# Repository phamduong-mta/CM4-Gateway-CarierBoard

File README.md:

# CM4 Security Gateway Rev B — GÓI FINAL (giai đoạn 2)

Xuất lúc 2026-11-19 14:27 · commit `5cdd320` (file chưa commit: 29) · KiCad 10.0.6

Bo mạch mang cho Raspberry Pi CM4 (eMMC, không WiFi): 1 WAN + 4 LAN Gigabit, USB-A, USB-C nạp eMMC, console micro-USB,
TPM 2.0, RTC, SRAM giữ khóa bị xóa khi mở vỏ (switch bàn phím cơ). 150 × 105 mm, 6 lớp, ENIG, nguồn 12 V DC.

## Trạng thái

| Hạng mục | Kết quả |
|---|---|
| ERC schematic | **0 lỗi**, 0 cảnh báo |
| DRC PCB (đã đi dây) | **0 lỗi**, 0 cảnh báo |
| Chưa nối | **0** |
| Lệch schematic ↔ PCB | **0** |
| Luật DRC theo Reference | không có |
| Linh kiện | 420 footprint; BOM JLC 397 = CPL 397 → đạt |
| Chân CM4 có nối | 100 / 200 |
| Tiền linh kiện | ≈ 56.7 USD/bo (5 bo, chưa gồm CM4, PCB, công lắp) |

## Đặt mạch: làm theo `06_fabrication/ORDERING.md`

Ba file cần tải lên JLCPCB: `06_fabrication/gerber.zip`, `bom_jlc.csv`, `cpl_jlc.csv`.
Trước khi thanh toán phải xem lại chiều xoay linh kiện ở màn hình xem trước của JLC (mục 4 của ORDERING.md).

## Nên xem

1. `03_images/3d_iso.png`, `3d_top.png`, `3d_bottom.png`, `3d_front.png`, `3d_back.png` — hình dạng bo.
2. `03_images/copper_L1…L6.png` — từng lớp đồng; `02_pcb_drawings/` — PDF từng lớp, bản vẽ lắp ráp, kích thước.
3. `01_schematic/cm4-gateway-schematic.pdf` — nguyên lý.
4. `05_reports/SUMMARY.md`, `routing-report.md` — DRC/ERC, độ dài và độ lệch từng cặp vi sai.
5. `09_docs/BRINGUP.md` — cấp nguồn lần đầu, nạp eMMC, thử từng khối, thử chống mở vỏ.
6. `09_docs/SOFTWARE.md` — `config.txt`, PCIe/NIC, TPM, RTC, SRAM + GPIO tamper.
7. `09_docs/design-doc.md`, `decisions.md` — thiết kế và mọi quyết định (kể cả thay đổi ở giai đoạn 2).

## Thay đổi so với gói giai đoạn 1 đã duyệt

- **Công tắc chống mở vỏ**: theo phản hồi của chủ dự án — Kailh Red (C49234236), model 3D switch bàn phím cơ thật.
  Nhấn (vỏ đậy) = thông mạch; nhả (mở vỏ) = ngắt → SRAM mất cả VCC lẫn VBAT.
- **Đảo cực P/N tại mọi đầu thu PCIe** (chuẩn PCIe cho phép, không cần cấu hình phần mềm) để cặp vi sai không bắt chéo.
- **Đổi gán cổng xuôi của switch** (SW1: cổng 1 → LAN2, cổng 2 → LAN1; SW2: cổng 1 → LAN4, cổng 2 → LAN3).
- **Dời linh kiện bên trong bo**: SW2 sang trái 6.4 mm; tụ AC và điện trở clock xếp thành cặp cạnh chân; khu USB xếp lại.
  Vị trí mọi cổng mặt trước/sau, kích thước bo và lỗ bắt vít **không đổi**.
- Chi tiết và lý do: `09_docs/decisions.md` (các dòng "(GĐ2)").

## Rủi ro còn mở (chi tiết ở design-doc §11)

- **R1** — chưa có bằng chứng công khai PI7C9X2G404SL ghép tầng chạy với CM4 (về nguyên tắc là cầu PCIe chuẩn).
- **R2** — mạch phân cực lại clock PCIe của CM4 chưa đo thực tế (đo ở BRINGUP bước 6).
- **R7** — bề rộng đường theo trở kháng tính bằng công thức gần đúng; cần chọn đúng stackup JLC06161H-3313 khi đặt.
- **Góc xoay CPL** chưa kiểm chứng được ngoại tuyến → xem lại trên trang JLC.
- Bản đi dây do script sinh, đã qua DRC của KiCad và review độc lập bằng máy; **chưa có người rà layout** — nên đặt
  số lượng nhỏ (5 bo) cho lần đầu.

## Cấu trúc gói

```
01_schematic/      PDF toàn bộ sheet + SVG
02_pcb_drawings/   PDF từng lớp đồng, bản vẽ lắp ráp top/bottom, kích thước, floorplan
03_images/         render 3D 5 góc, ảnh từng lớp đồng, sơ đồ khối, cây nguồn
04_3d/             STEP đầy đủ
05_reports/        ERC + DRC (rpt + json), tóm tắt, báo cáo đi dây
06_fabrication/    gerber.zip (+ thư mục gerber, bản đồ khoan), bom_jlc.csv, cpl_jlc.csv, lcsc_map.csv, ORDERING.md
07_bom_netlist/    BOM đầy đủ kèm tồn kho/giá, netlist, toạ độ mọi linh kiện
08_source/         nguồn KiCad + thư viện + model 3D + toàn bộ script sinh thiết kế
09_docs/           design doc, bảng chân CM4, driver-check, BRINGUP.md, SOFTWARE.md, quyết định, review
```

Sinh lại toàn bộ từ nguồn: `python3 scripts/gen/design.py && python3 scripts/gen/board.py &&
git show 5cdd320:hardware/cm4-gateway.kicad_pcb > /tmp/revA.kicad_pcb && .venv/bin/python scripts/gen/reuse_route.py /tmp/revA.kicad_pcb && .venv/bin/python scripts/gen/finish.py 8 && .venv/bin/python scripts/gen/patch_rev_b.py && python3 scripts/gen/polish_rev_b.py hardware/cm4-gateway.kicad_pcb && python3 scripts/export_release.py` (Rev B giữ nguyên dây của Rev A ngoài khu nguồn, chỉ đi lại khu nguồn; Rev A sinh bằng `route.py` + `patch_rev_a.py`).

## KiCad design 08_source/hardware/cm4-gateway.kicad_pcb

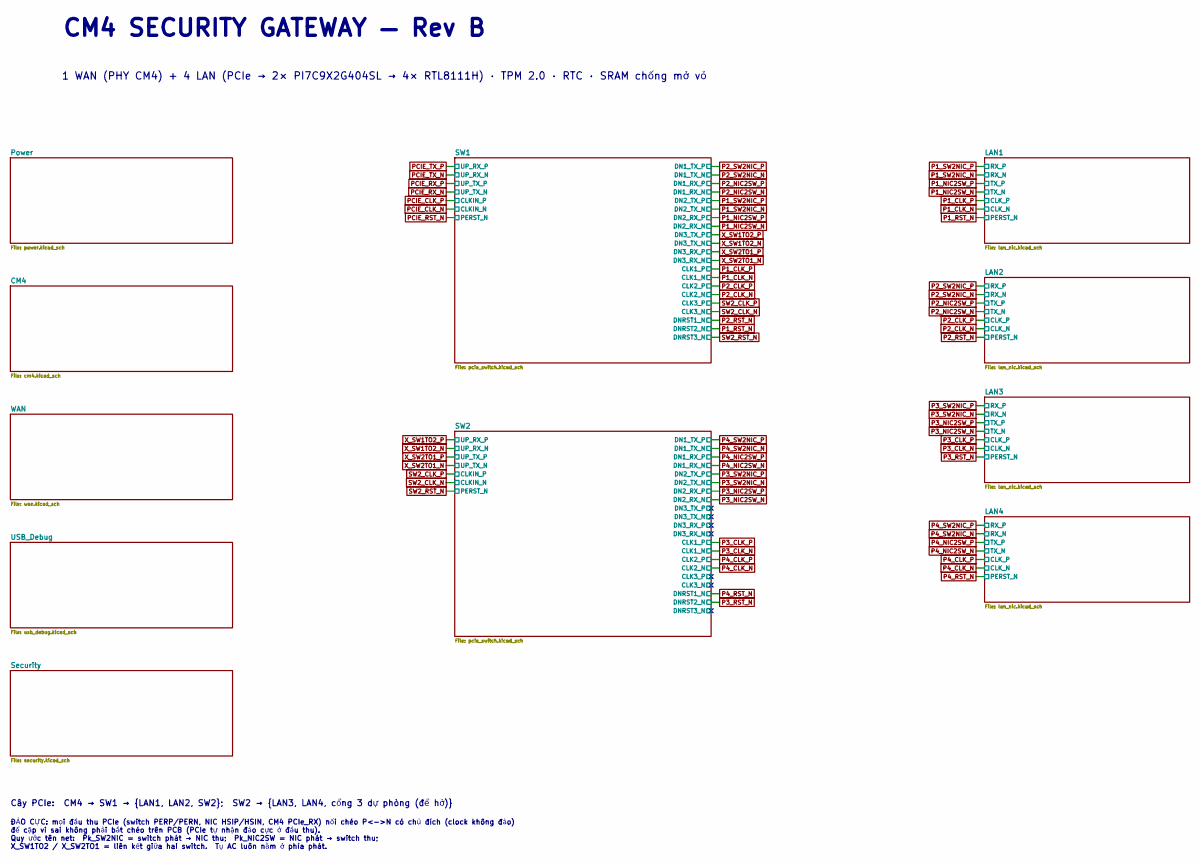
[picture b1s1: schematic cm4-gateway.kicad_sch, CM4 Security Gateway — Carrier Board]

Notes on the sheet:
CM4 SECURITY GATEWAY — Rev B
1 WAN (PHY CM4) + 4 LAN (PCIe → 2× PI7C9X2G404SL → 4× RTL8111H) · TPM 2.0 · RTC · SRAM chống mở vỏ
Cây PCIe: CM4 → SW1 → {LAN1, LAN2, SW2}; SW2 → {LAN3, LAN4, cổng 3 dự phòng (để hở)}
ĐẢO CỰC: mọi đầu thu PCIe (switch PERP/PERN, NIC HSIP/HSIN, CM4 PCIe_RX) nối chéo P<->N có chủ đích (clock không đảo) để cặp vi sai không phải bắt chéo trên PCB (PCIe tự nhận đảo cực ở đầu thu). Quy ước tên net: Pk_SW2NIC = switch phát → NIC thu; Pk_NIC2SW = NIC phát → switch thu; X_SW1TO2 / X_SW2T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

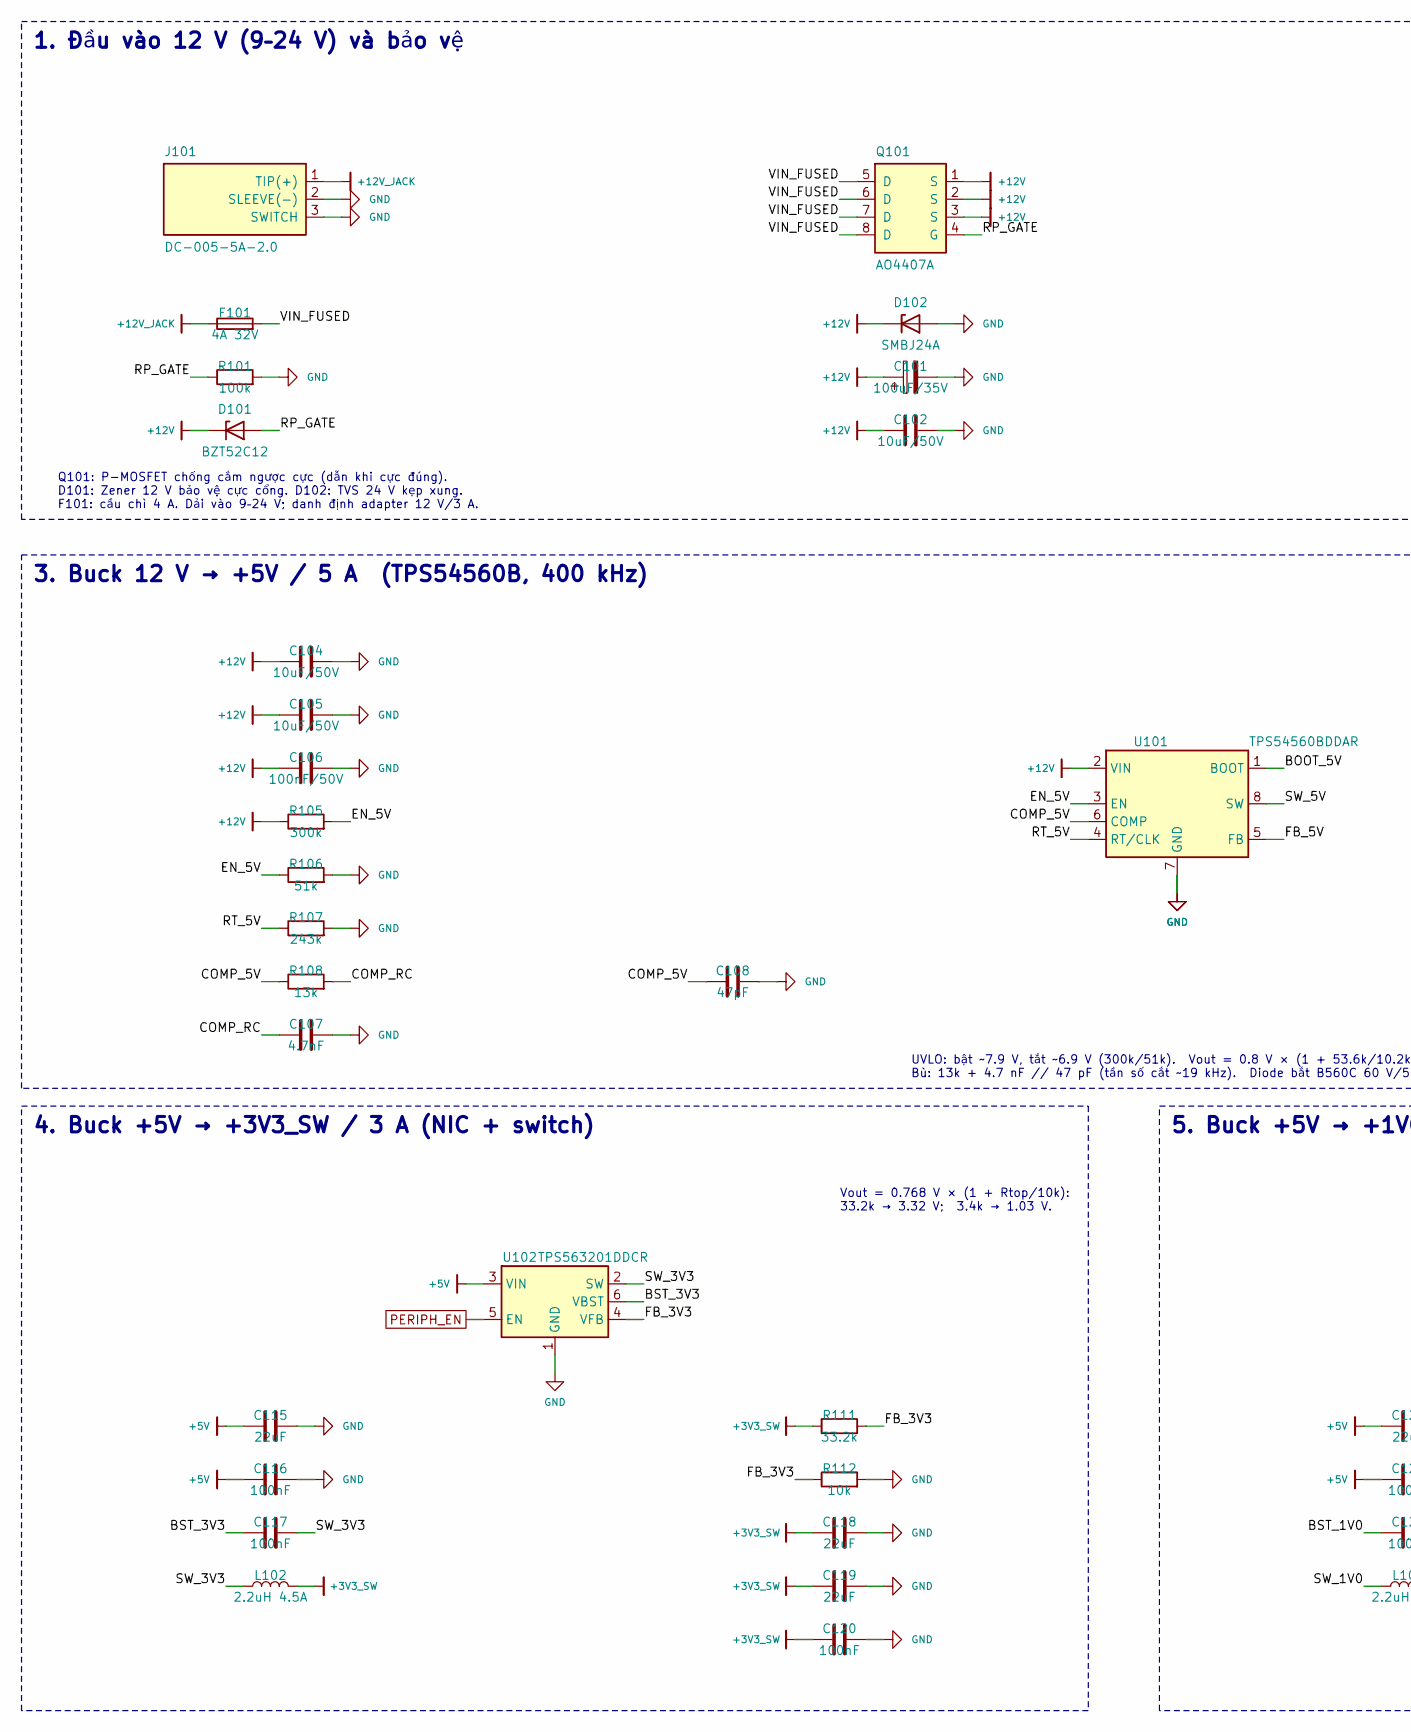
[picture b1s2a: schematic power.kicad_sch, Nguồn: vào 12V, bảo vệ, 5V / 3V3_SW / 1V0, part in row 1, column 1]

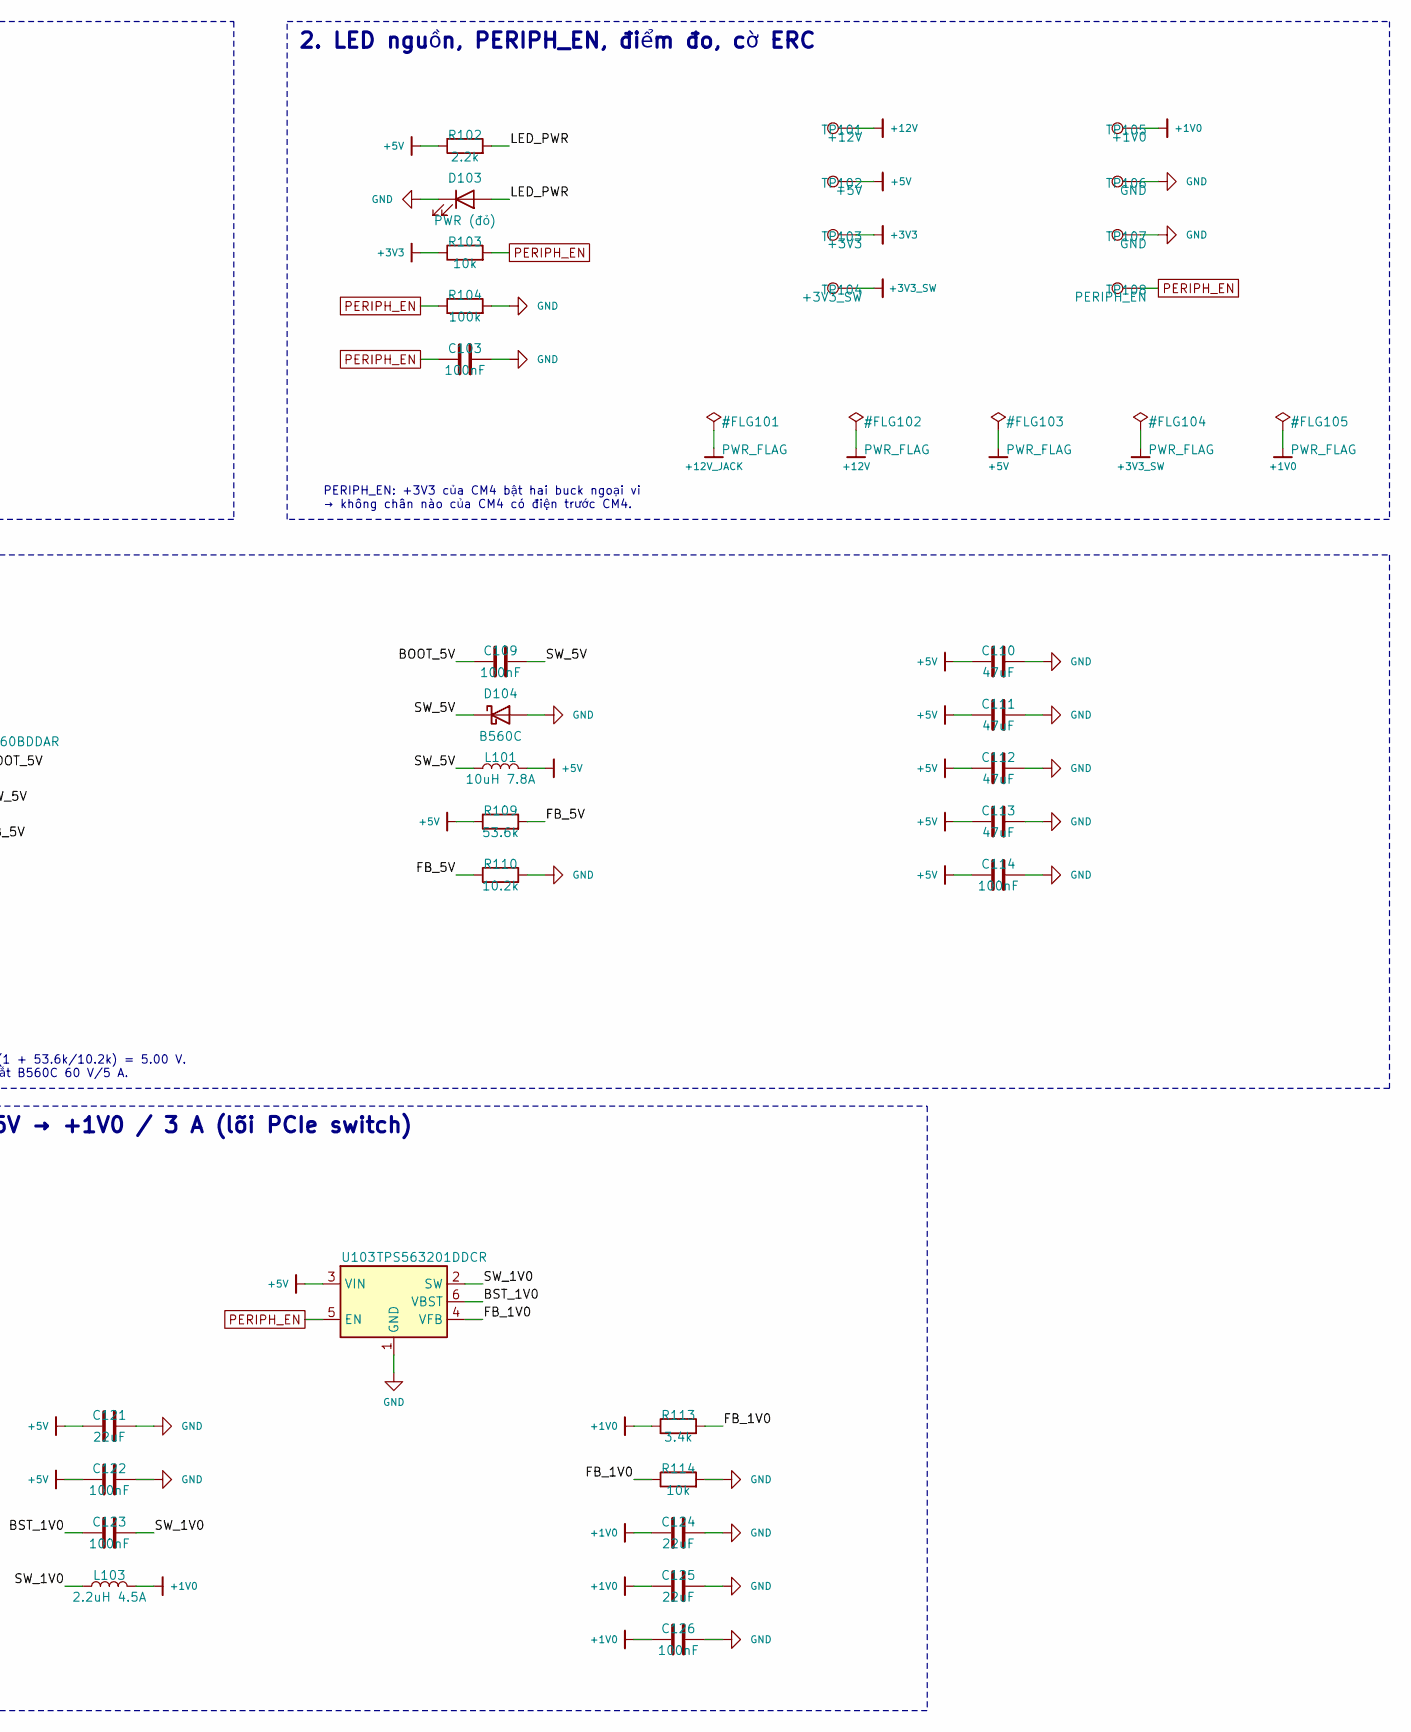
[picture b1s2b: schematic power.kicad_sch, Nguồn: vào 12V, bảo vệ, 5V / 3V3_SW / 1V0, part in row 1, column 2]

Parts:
C101: 100uF/35V; CP_Elec_6.3x7.7; MPN VZH101M1VTR-0607; LCSC C176683
C102, C104, C105: 10uF/50V; C_1206_3216Metric; MPN CL31A106KBHNNNE; LCSC C13585
C103, C109, C114, C116, C117, C120, C122, C123, C126: 100nF; C_0402_1005Metric; MPN CL05B104KO5NNNC; LCSC C1525
C106: 100nF/50V; C_0402_1005Metric; MPN GRM155R71H104KE14D; LCSC C77020
C107: 4.7nF; C_0402_1005Metric; MPN CL05B472KB5NNNC; LCSC C84705
C108: 47pF; C_0402_1005Metric; MPN CL05C470JB5NNNC; LCSC C84706
C110, C111, C112, C113: 47uF; C_1206_3216Metric; MPN CL31A476MPHNNNE; LCSC C96123
C115, C118, C119, C121, C124, C125: 22uF; C_0805_2012Metric; MPN CL21A226MAQNNNE; LCSC C45783
D101: BZT52C12; D_SOD-123; MPN BZT52C12; LCSC C43491
D102: SMBJ24A; D_SMB; MPN SMBJ24A; LCSC C123819
D103: PWR (đỏ); LED_0603_1608Metric; MPN KT-0603R; LCSC C2286
D104: B560C; D_SMC; MPN B560C-13-F; LCSC C85100
F101: 4A 32V; Fuse_1206_3216Metric; MPN 0466004.NRHF; LCSC C187596
J101: DC-005-5A-2.0; BarrelJack_XKB_DC-005-5A; MPN DC-005-5A-2.0; LCSC C381116
L101: 10uH 7.8A; L_Changjiang_FXL1040; MPN FXL1040-100-M; LCSC C475915
L102, L103: 2.2uH 4.5A; L_Changjiang_FXL0420; MPN FXL0420-2R2-M; LCSC C167206
Q101: AO4407A; SOIC-8_3.9x4.9mm_P1.27mm; MPN AO4407A; LCSC C16072
R101, R104: 100k; R_0402_1005Metric; MPN 0402WGF1003TCE; LCSC C25741
R102: 2.2k; R_0402_1005Metric; MPN 0402WGF2201TCE; LCSC C25879
R103, R112, R114: 10k; R_0402_1005Metric; MPN 0402WGF1002TCE; LCSC C25744
R105: 300k; R_0402_1005Metric; MPN 0402WGF3003TCE; LCSC C25774
R106: 51k; R_0402_1005Metric; MPN 0402WGF5102TCE; LCSC C25794
R107: 243k; R_0402_1005Metric; MPN 0402WGF2433TCE; LCSC C43249
R108: 13k; R_0402_1005Metric; MPN 0402WGF1302TCE; LCSC C25754
R109: 53.6k; R_0402_1005Metric; MPN 0402WGF5362TCE; LCSC C53398
R110: 10.2k; R_0402_1005Metric; MPN 0402WGF1022TCE; LCSC C11660
R111: 33.2k; R_0402_1005Metric; MPN 0402WGF3322TCE; LCSC C122548
R113: 3.4k; R_0402_1005Metric; MPN 0402WGF3401TCE; LCSC C4940
TP101: +12V; TestPoint_Pad_D1.0mm
TP102: +5V; TestPoint_Pad_D1.0mm
TP103: +3V3; TestPoint_Pad_D1.0mm
TP104: +3V3_SW; TestPoint_Pad_D1.0mm
TP105: +1V0; TestPoint_Pad_D1.0mm
TP106, TP107: GND; TestPoint_Pad_D1.0mm
TP108: PERIPH_EN; TestPoint_Pad_D1.0mm
U101: TPS54560BDDAR; HSOP-8-1EP_3.9x4.9mm_P1.27mm_EP2.41x3.1mm_ThermalVias; MPN TPS54560BDDAR; LCSC C1850354
U102, U103: TPS563201DDCR; TSOT-23-6; MPN TPS563201DDCR; LCSC C116592

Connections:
+1V0: C124.1, C125.1, C126.1, L103.2, R113.1, TP105.1; also elsewhere on the board
+3V3: R103.1, TP103.1; also elsewhere on the board
+3V3_SW: C118.1, C119.1, C120.1, L102.2, R111.1, TP104.1; also elsewhere on the board
+5V: C110.1, C111.1, C112.1, C113.1, C114.1, C115.1, C116.1, C121.1, C122.1, L101.2, R102.1, R109.1, TP102.1, U102.3 (VIN), U103.3 (VIN); also elsewhere on the board
+12V: C101.1, C102.1, C104.1, C105.1, C106.1, D101.1 (K), D102.1 (K), Q101.1 (S), Q101.2 (S), Q101.3 (S), R105.1, TP101.1, U101.2 (VIN)
+12V_JACK: F101.1, J101.1 (TIP(+))
/Power/BOOT_5V: C109.1, U101.1 (BOOT)
/Power/BST_1V0: C123.1, U103.6 (VBST)
/Power/BST_3V3: C117.1, U102.6 (VBST)
/Power/COMP_5V: C108.1, R108.1, U101.6 (COMP)
/Power/COMP_RC: C107.1, R108.2
/Power/EN_5V: R105.2, R106.1, U101.3 (EN)
/Power/FB_1V0: R113.2, R114.1, U103.4 (VFB)
/Power/FB_3V3: R111.2, R112.1, U102.4 (VFB)
/Power/FB_5V: R109.2, R110.1, U101.5 (FB)
/Power/LED_PWR: D103.2 (A), R102.2
/Power/RP_GATE: D101.2 (A), Q101.4 (G), R101.1
/Power/RT_5V: R107.1, U101.4 (RT/CLK)
/Power/SW_1V0: C123.2, L103.1, U103.2 (SW)
/Power/SW_3V3: C117.2, L102.1, U102.2 (SW)
/Power/SW_5V: C109.2, D104.1 (K), L101.1, U101.8 (SW)
/Power/VIN_FUSED: F101.2, Q101.5 (D), Q101.6 (D), Q101.7 (D), Q101.8 (D)
GND: C101.2, C102.2, C103.2, C104.2, C105.2, C106.2, C107.2, C108.2, C110.2, C111.2, C112.2, C113.2, C114.2, C115.2, C116.2, C118.2, C119.2, C120.2, C121.2, C122.2, C124.2, C125.2, C126.2, D102.2 (A), D103.1 (K), D104.2 (A), J101.2 (SLEEVE(-)), J101.3 (SWITCH), R101.2, R104.2, R106.2, R107.2, R110.2, R112.2, R114.2, TP106.1, TP107.1, U101.7 (GND), U101.9 (GND), U102.1 (GND), U103.1 (GND); also elsewhere on the board
PERIPH_EN: C103.1, R103.2, R104.1, TP108.1, U102.5 (EN), U103.5 (EN)

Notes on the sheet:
1. Đầu vào 12 V (9–24 V) và bảo vệ
Q101: P-MOSFET chống cắm ngược cực (dẫn khi cực đúng). D101: Zener 12 V bảo vệ cực cổng. D102: TVS 24 V kẹp xung. F101: cầu chì 4 A. Dải vào 9–24 V; danh định adapter 12 V/3 A.
2. LED nguồn, PERIPH_EN, điểm đo, cờ ERC
PERIPH_EN: +3V3 của CM4 bật hai buck ngoại vi → không chân nào của CM4 có điện trước CM4.
3. Buck 12 V → +5V / 5 A (TPS54560B, 400 kHz)
UVLO: bật ~7.9 V, tắt ~6.9 V (300k/51k). Vout = 0.8 V × (1 + 53.6k/10.2k) = 5.00 V. Bù: 13k + 4.7 nF // 47 pF (tần số cắt ~19 kHz). Diode bắt B560C 60 V/5 A.
4. Buck +5V → +3V3_SW / 3 A (NIC + switch)
5. Buck +5V → +1V0 / 3 A (lõi PCIe switch)
Vout = 0.768 V × (1 + Rtop/10k): 33.2k → 3.32 V; 3.4k → 1.03 V.

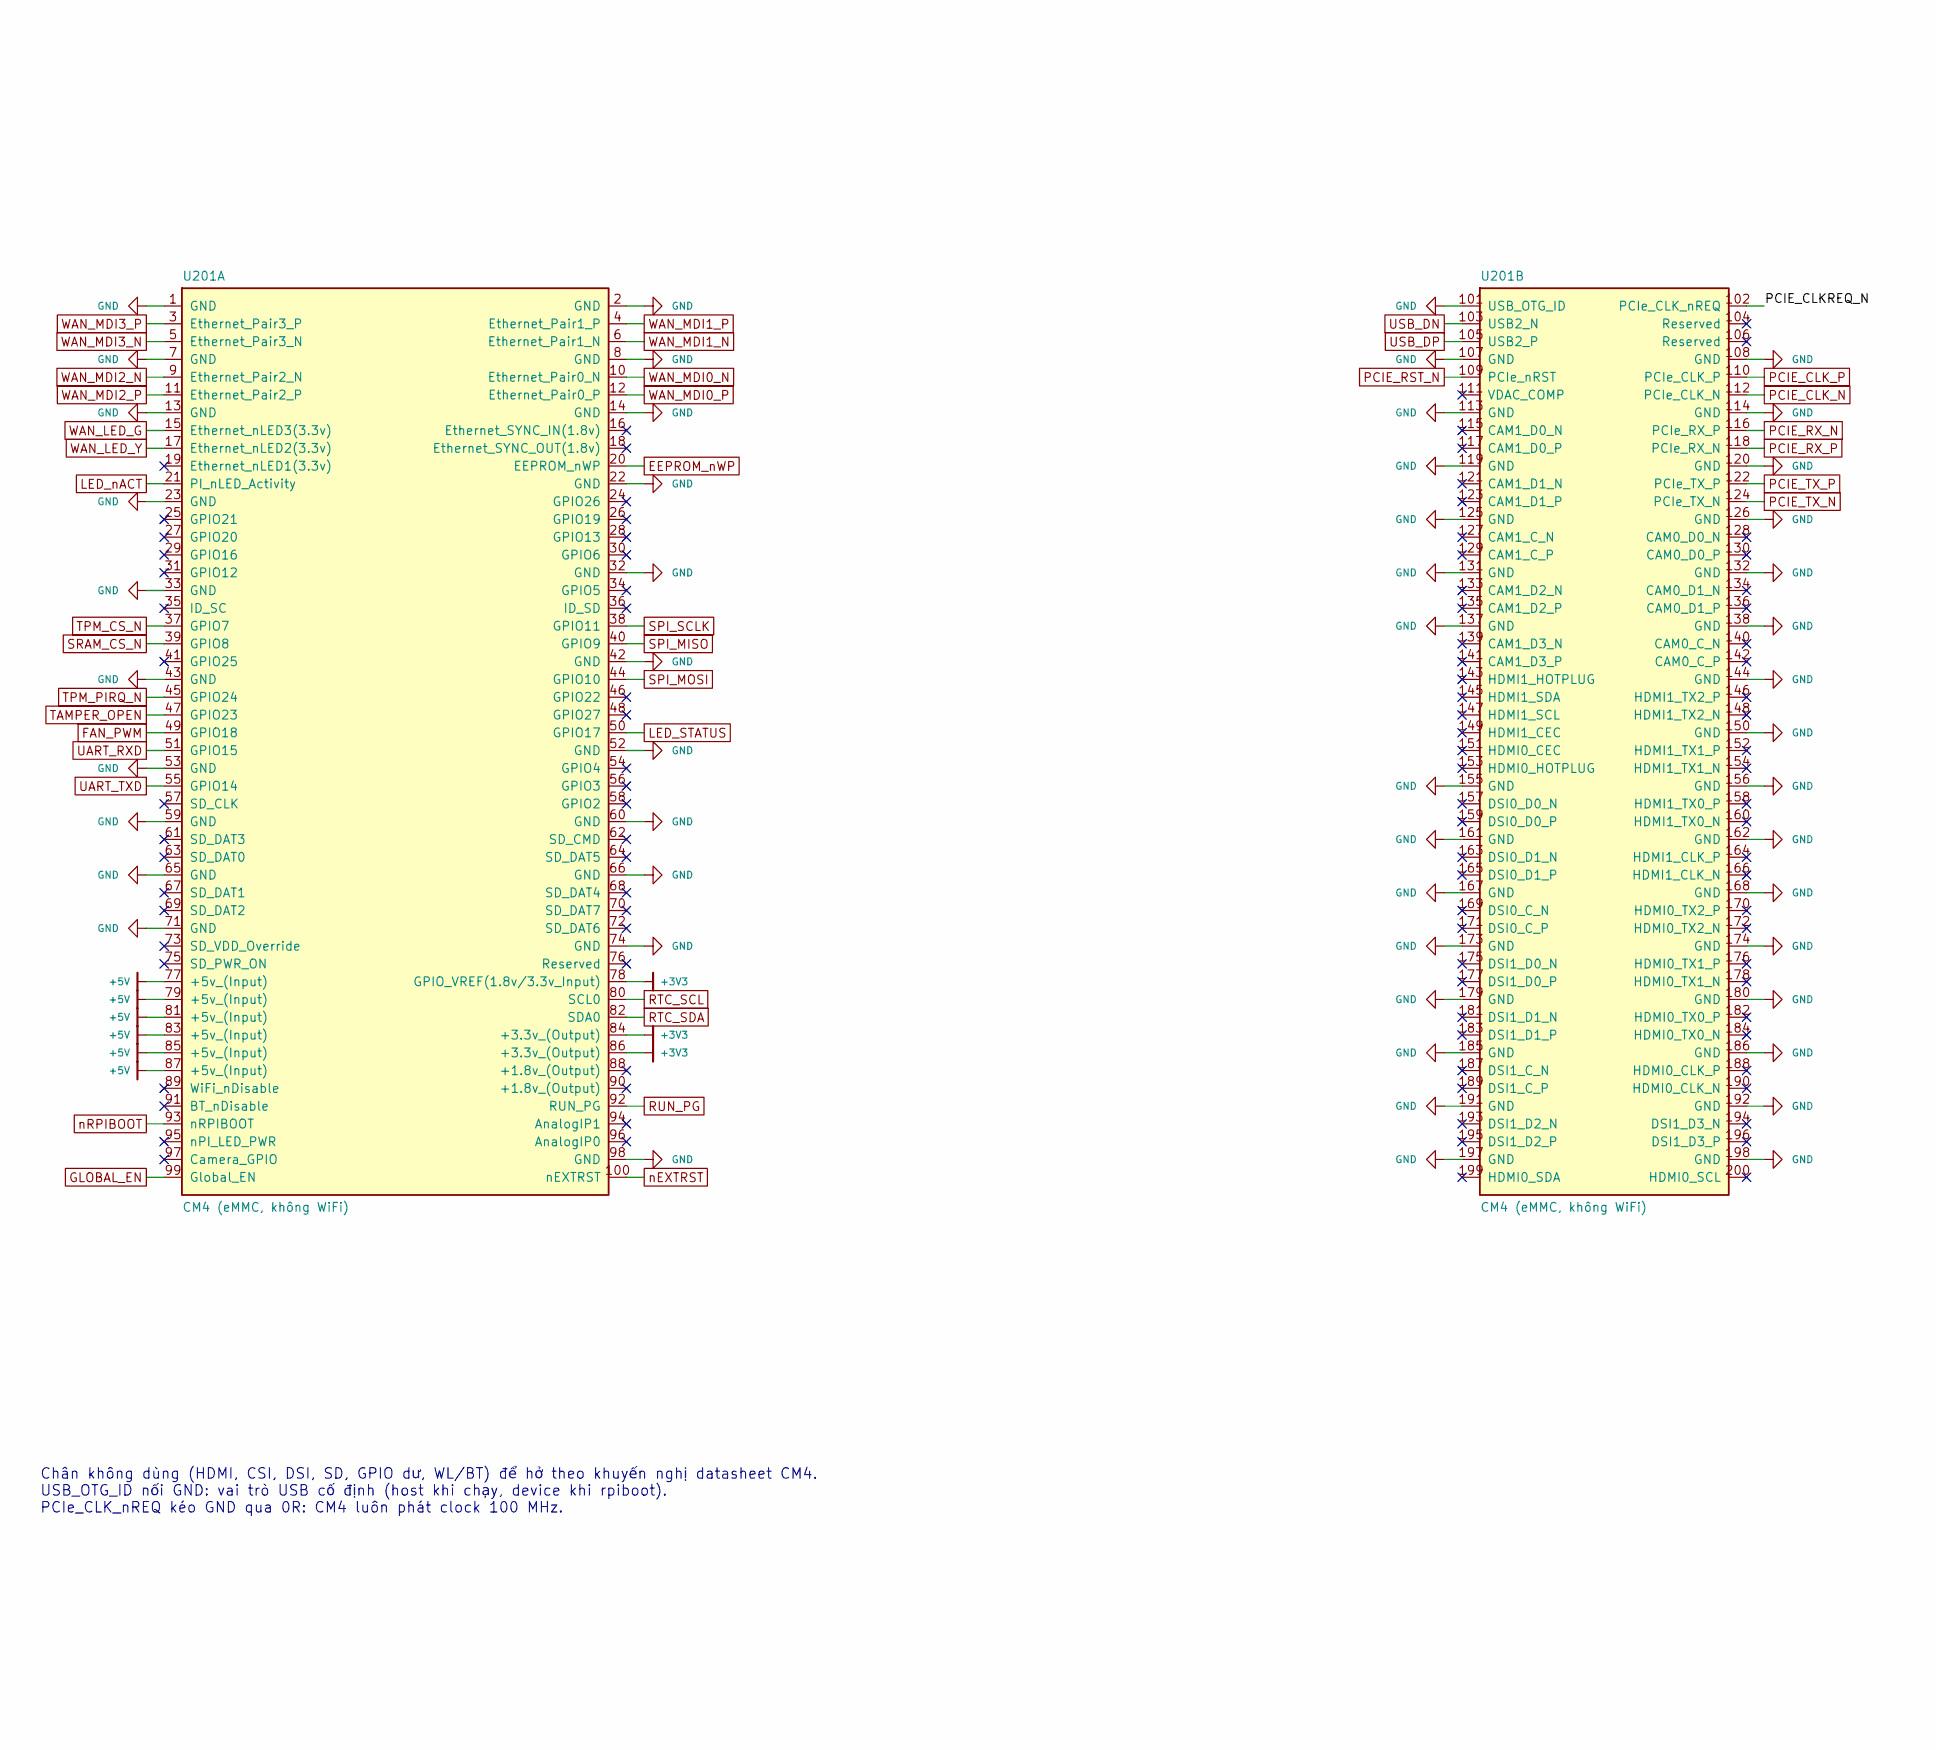
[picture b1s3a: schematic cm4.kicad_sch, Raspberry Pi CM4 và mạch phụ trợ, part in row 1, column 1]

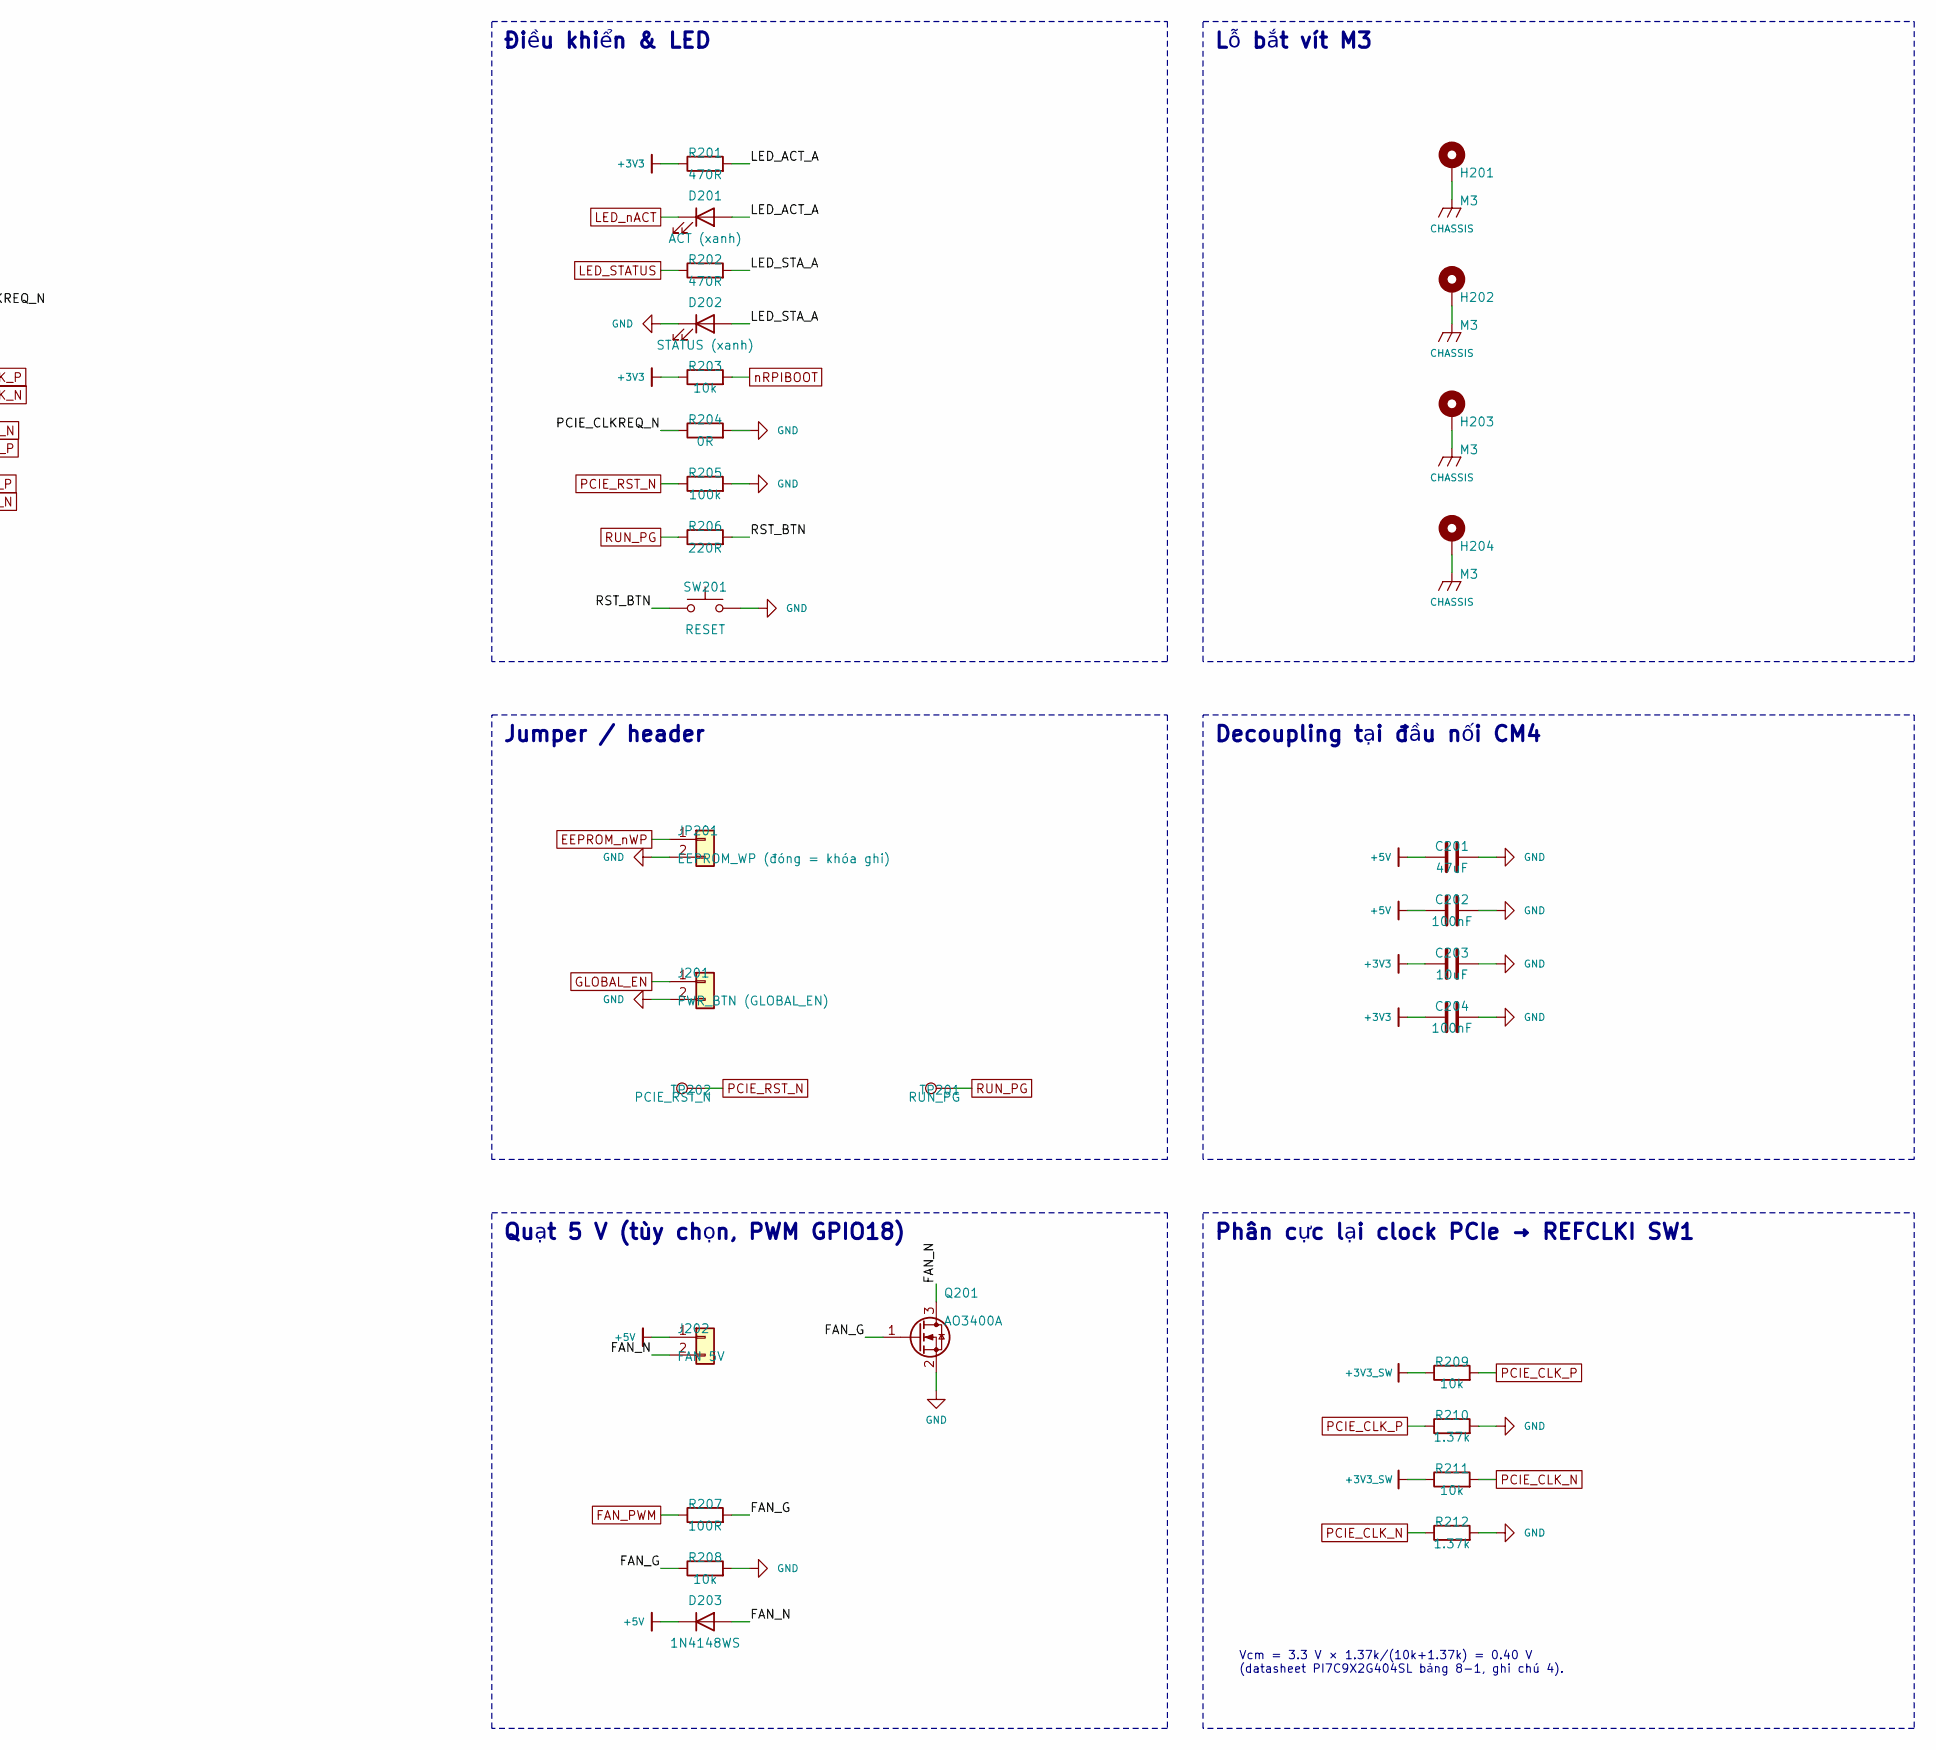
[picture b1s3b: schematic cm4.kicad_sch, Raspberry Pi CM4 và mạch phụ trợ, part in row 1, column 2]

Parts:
C201: 47uF; C_1206_3216Metric; MPN CL31A476MPHNNNE; LCSC C96123
C202, C204: 100nF; C_0402_1005Metric; MPN CL05B104KO5NNNC; LCSC C1525
C203: 10uF; C_0603_1608Metric; MPN CL10A106KP8NNNC; LCSC C19702
D201: ACT (xanh); LED_0603_1608Metric; MPN KT-0603G; LCSC C12624
D202: STATUS (xanh); LED_0603_1608Metric; MPN KT-0603G; LCSC C12624
D203: 1N4148WS; D_SOD-323; MPN 1N4148WS; LCSC C2128
H201, H202, H203, H204: M3; MountingHole_3.2mm_M3_Pad_Via
J201: PWR_BTN (GLOBAL_EN); PinHeader_1x02_P2.54mm_Vertical; MPN B-2100S02P-A110; LCSC C124375
J202: FAN 5V; PinHeader_1x02_P2.54mm_Vertical; MPN B-2100S02P-A110; LCSC C124375
JP201: EEPROM_WP (đóng = khóa ghi); PinHeader_1x02_P2.54mm_Vertical; MPN B-2100S02P-A110; LCSC C124375
Q201: AO3400A; SOT-23; MPN AO3400A; LCSC C20917
R201, R202: 470R; R_0402_1005Metric; MPN 0402WGF4700TCE; LCSC C25117
R203, R208, R209, R211: 10k; R_0402_1005Metric; MPN 0402WGF1002TCE; LCSC C25744
R204: 0R; R_0402_1005Metric; MPN 0402WGF0000TCE; LCSC C17168
R205: 100k; R_0402_1005Metric; MPN 0402WGF1003TCE; LCSC C25741
R206: 220R; R_0402_1005Metric; MPN 0402WGF2200TCE; LCSC C25091
R207: 100R; R_0402_1005Metric; MPN 0402WGF1000TCE; LCSC C25076
R210, R212: 1.37k; R_0402_1005Metric; MPN 0402WGF1371TCE; LCSC C423239
SW201: RESET; SW_SPST_SKQG_WithStem; MPN SKQGABE010; LCSC C115351
TP201: RUN_PG; TestPoint_Pad_D1.0mm
TP202: PCIE_RST_N; TestPoint_Pad_D1.0mm
U201: CM4 (eMMC, không WiFi); Raspberry-Pi-4-Compute-Module; MPN DF40C-100DS-0.4V(58); LCSC C3642394

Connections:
+3V3: C203.1, C204.1, R201.1, R203.1, U201.78 (GPIO_VREF(1.8v/3.3v_Input)), U201.84 (+3.3v_(Output)), U201.86 (+3.3v_(Output)); also elsewhere on the board
+3V3_SW: R209.1, R211.1; also elsewhere on the board
+5V: C201.1, C202.1, D203.1 (K), J202.1, U201.77 (+5v_(Input)), U201.79 (+5v_(Input)), U201.81 (+5v_(Input)), U201.83 (+5v_(Input)), U201.85 (+5v_(Input)), U201.87 (+5v_(Input)); also elsewhere on the board
/CM4/FAN_G: Q201.1 (G), R207.2, R208.1
/CM4/FAN_N: D203.2 (A), J202.2, Q201.3 (D)
/CM4/LED_ACT_A: D201.2 (A), R201.2
/CM4/LED_STA_A: D202.2 (A), R202.2
/CM4/PCIE_CLKREQ_N: R204.1, U201.102 (PCIe_CLK_nREQ)
/CM4/RST_BTN: R206.2, SW201.1
CHASSIS: H201.1, H202.1, H203.1, H204.1; also elsewhere on the board
EEPROM_nWP: JP201.1, U201.20 (EEPROM_nWP)
FAN_PWM: R207.1, U201.49 (GPIO18)
GLOBAL_EN: J201.1, U201.99 (Global_EN)
GND: C201.2, C202.2, C203.2, C204.2, D202.1 (K), J201.2, JP201.2, Q201.2 (S), R204.2, R205.2, R208.2, R210.2, R212.2, SW201.2, U201.1 (GND), U201.2 (GND), U201.7 (GND), U201.8 (GND), U201.13 (GND), U201.14 (GND), U201.22 (GND), U201.23 (GND), U201.32 (GND), U201.33 (GND), U201.42 (GND), U201.43 (GND), U201.52 (GND), U201.53 (GND), U201.59 (GND), U201.60 (GND), U201.65 (GND), U201.66 (GND), U201.71 (GND), U201.74 (GND), U201.98 (GND), U201.101 (USB_OTG_ID), U201.107 (GND), U201.108 (GND), U201.113 (GND), U201.114 (GND), U201.119 (GND), U201.120 (GND), U201.125 (GND), U201.126 (GND), U201.131 (GND), U201.132 (GND), U201.137 (GND), U201.138 (GND), U201.144 (GND), U201.150 (GND), U201.155 (GND), U201.156 (GND), U201.161 (GND), U201.162 (GND), U201.167 (GND), U201.168 (GND), U201.173 (GND), U201.174 (GND), U201.179 (GND), U201.180 (GND), U201.185 (GND), U201.186 (GND), U201.191 (GND), U201.192 (GND), U201.197 (GND), U201.198 (GND); also elsewhere on the board
LED_STATUS: R202.1, U201.50 (GPIO17)
LED_nACT: D201.1 (K), U201.21 (PI_nLED_Activity)
PCIE_CLK_N: R211.2, R212.1, U201.112 (PCIe_CLK_N); also elsewhere on the board
PCIE_CLK_P: R209.2, R210.1, U201.110 (PCIe_CLK_P); also elsewhere on the board
PCIE_RST_N: R205.1, TP202.1, U201.109 (PCIe_nRST); also elsewhere on the board
PCIE_RX_N: U201.116 (PCIe_RX_P); also elsewhere on the board
PCIE_RX_P: U201.118 (PCIe_RX_N); also elsewhere on the board
PCIE_TX_N: U201.124 (PCIe_TX_N); also elsewhere on the board
PCIE_TX_P: U201.122 (PCIe_TX_P); also elsewhere on the board
RTC_SCL: U201.80 (SCL0); also elsewhere on the board
RTC_SDA: U201.82 (SDA0); also elsewhere on the board
RUN_PG: R206.1, TP201.1, U201.92 (RUN_PG)
SPI_MISO: U201.40 (GPIO9); also elsewhere on the board
SPI_MOSI: U201.44 (GPIO10); also elsewhere on the board
SPI_SCLK: U201.38 (GPIO11); also elsewhere on the board
SRAM_CS_N: U201.39 (GPIO8); also elsewhere on the board
TAMPER_OPEN: U201.47 (GPIO23); also elsewhere on the board
TPM_CS_N: U201.37 (GPIO7); also elsewhere on the board
TPM_PIRQ_N: U201.45 (GPIO24); also elsewhere on the board
UART_RXD: U201.51 (GPIO15); also elsewhere on the board
UART_TXD: U201.55 (GPIO14); also elsewhere on the board
USB_DN: U201.103 (USB2_N); also elsewhere on the board
USB_DP: U201.105 (USB2_P); also elsewhere on the board
WAN_LED_G: U201.15 (Ethernet_nLED3(3.3v)); also elsewhere on the board
WAN_LED_Y: U201.17 (Ethernet_nLED2(3.3v)); also elsewhere on the board
WAN_MDI0_N: U201.10 (Ethernet_Pair0_N); also elsewhere on the board
WAN_MDI0_P: U201.12 (Ethernet_Pair0_P); also elsewhere on the board
WAN_MDI1_N: U201.6 (Ethernet_Pair1_N); also elsewhere on the board
WAN_MDI1_P: U201.4 (Ethernet_Pair1_P); also elsewhere on the board
WAN_MDI2_N: U201.9 (Ethernet_Pair2_N); also elsewhere on the board
WAN_MDI2_P: U201.11 (Ethernet_Pair2_P); also elsewhere on the board
WAN_MDI3_N: U201.5 (Ethernet_Pair3_N); also elsewhere on the board
WAN_MDI3_P: U201.3 (Ethernet_Pair3_P); also elsewhere on the board
nEXTRST: U201.100 (nEXTRST); also elsewhere on the board
nRPIBOOT: R203.2, U201.93 (nRPIBOOT); also elsewhere on the board

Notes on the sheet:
Điều khiển & LED
Jumper / header
Quạt 5 V (tùy chọn, PWM GPIO18)
Phân cực lại clock PCIe → REFCLKI SW1
Vcm = 3.3 V × 1.37k/(10k+1.37k) = 0.40 V (datasheet PI7C9X2G404SL bảng 8-1, ghi chú 4).
Decoupling tại đầu nối CM4
Lỗ bắt vít M3
Chân không dùng (HDMI, CSI, DSI, SD, GPIO dư, WL/BT) để hở theo khuyến nghị datasheet CM4. USB_OTG_ID nối GND: vai trò USB cố định (host khi chạy, device khi rpiboot). PCIe_CLK_nREQ kéo GND qua 0R: CM4 luôn phát clock 100 MHz.

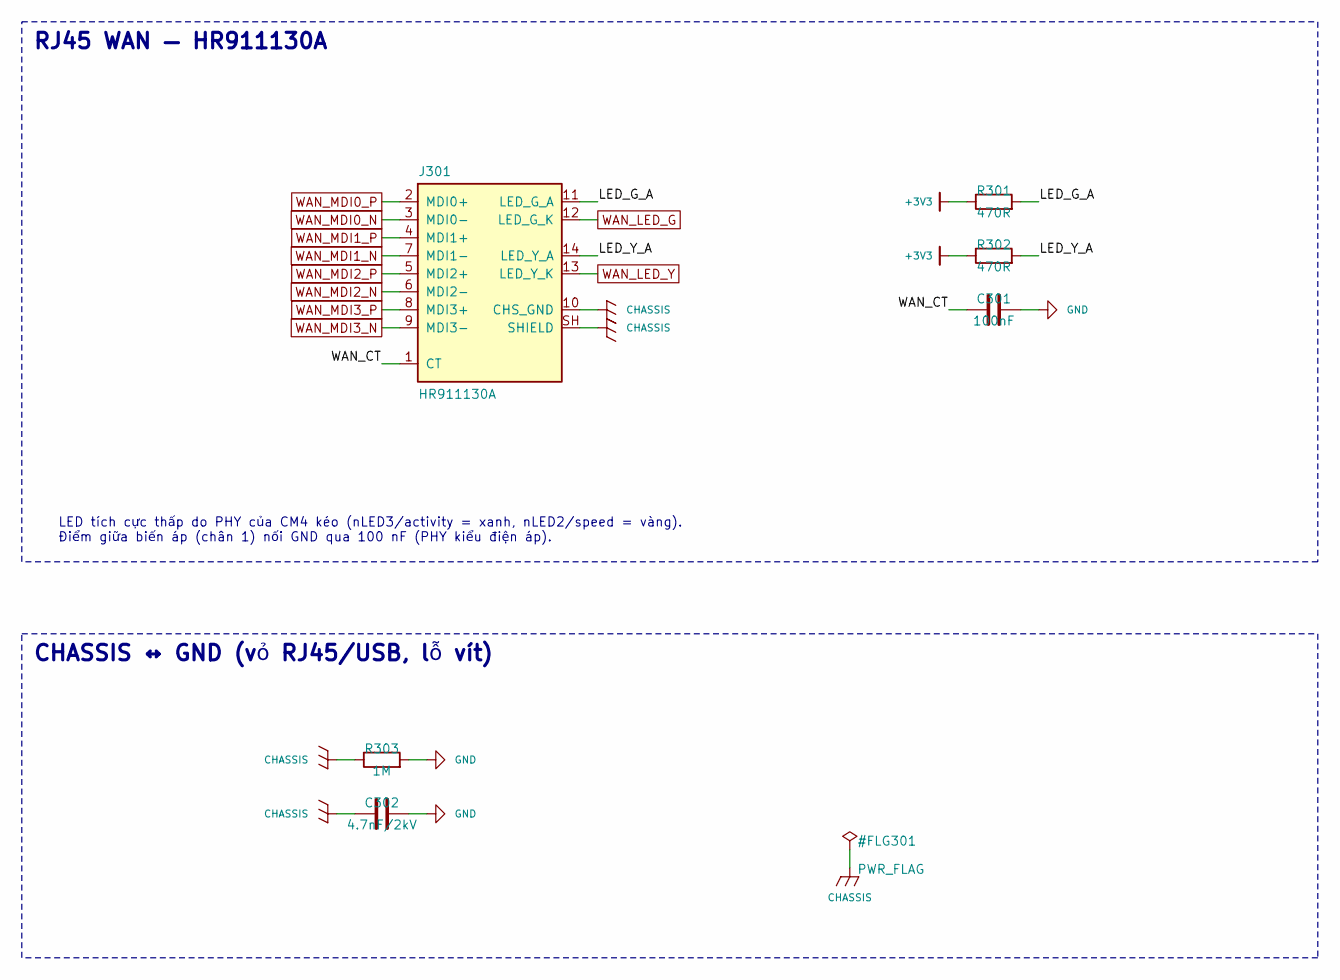
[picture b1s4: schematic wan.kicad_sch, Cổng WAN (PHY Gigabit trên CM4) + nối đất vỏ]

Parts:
C301: 100nF; C_0402_1005Metric; MPN CL05B104KO5NNNC; LCSC C1525
C302: 4.7nF/2kV; C_1206_3216Metric; MPN 1206B472K202NT; LCSC C41017
J301: HR911130A; RJ45_Hanrun_HR911130A_Horizontal; MPN HR911130A; LCSC C54408
R301, R302: 470R; R_0402_1005Metric; MPN 0402WGF4700TCE; LCSC C25117
R303: 1M; R_0402_1005Metric; MPN 0402WGF1004TCE; LCSC C26083

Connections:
+3V3: R301.1, R302.1; also elsewhere on the board
/WAN/LED_G_A: J301.11 (LED_G_A), R301.2
/WAN/LED_Y_A: J301.14 (LED_Y_A), R302.2
/WAN/WAN_CT: C301.1, J301.1 (CT)
CHASSIS: C302.1, J301.10 (CHS_GND), J301.SH (SHIELD), R303.1; also elsewhere on the board
GND: C301.2, C302.2, R303.2; also elsewhere on the board
WAN_LED_G: J301.12 (LED_G_K); also elsewhere on the board
WAN_LED_Y: J301.13 (LED_Y_K); also elsewhere on the board
WAN_MDI0_N: J301.3 (MDI0-); also elsewhere on the board
WAN_MDI0_P: J301.2 (MDI0+); also elsewhere on the board
WAN_MDI1_N: J301.7 (MDI1-); also elsewhere on the board
WAN_MDI1_P: J301.4 (MDI1+); also elsewhere on the board
WAN_MDI2_N: J301.6 (MDI2-); also elsewhere on the board
WAN_MDI2_P: J301.5 (MDI2+); also elsewhere on the board
WAN_MDI3_N: J301.9 (MDI3-); also elsewhere on the board
WAN_MDI3_P: J301.8 (MDI3+); also elsewhere on the board

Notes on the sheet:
RJ45 WAN — HR911130A
LED tích cực thấp do PHY của CM4 kéo (nLED3/activity = xanh, nLED2/speed = vàng). Điểm giữa biến áp (chân 1) nối GND qua 100 nF (PHY kiểu điện áp).
CHASSIS ↔ GND (vỏ RJ45/USB, lỗ vít)
